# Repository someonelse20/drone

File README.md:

# drone
All the files for my drone project.

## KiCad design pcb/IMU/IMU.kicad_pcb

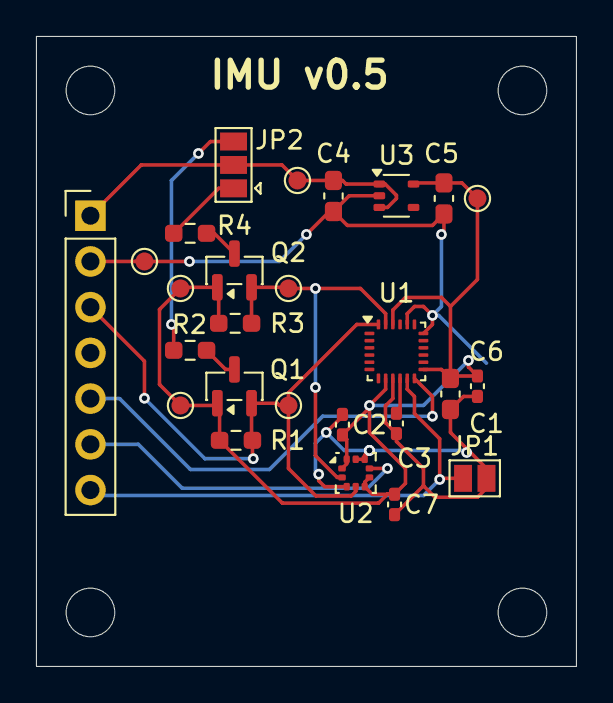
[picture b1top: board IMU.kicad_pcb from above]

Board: 2 copper layers, 30.0 x 35.0 mm, 26 parts (0 on the bottom side), 13 nets.

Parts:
C1, C4, C5: 1uf; C_0603_1608Metric_Pad1.08x0.95mm_HandSolder
C2, C3, C6, C7: 0.1uf; C_0402_1005Metric_Pad0.74x0.62mm_HandSolder
J1: Pin Bus; PinHeader_1x07_P2.54mm_Vertical
JP1: SolderJumper_2_Open; SolderJumper-2_P1.3mm_Open_Pad1.0x1.5mm
JP2: SolderJumper_3_Open; SolderJumper-3_P1.3mm_Open_Pad1.0x1.5mm
Q1, Q2: BSS84; SOT-23
R1, R2, R3, R4: 2.2k; R_0603_1608Metric_Pad0.98x0.95mm_HandSolder
TP1, TP2, TP3, TP4, TP5, TP6, TP7: TestPoint; TestPoint_Pad_D1.0mm
U1: ICM-20948; InvenSense_QFN-24_3x3mm_P0.4mm
U2: ST_HLGA-10_2x2mm_P0.5mm_LayoutBorder3x2y
U3: MIC5365-1.8YC5; SOT-353_SC-70-5

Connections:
/1.8v: C1.1, C2.1, C5.1, C6.1, C7.1, Q1.1 (G), Q2.1 (G), R1.1, R3.1, TP1.1, TP4.1, TP7.1, U1.8 (VDDIO), U1.13 (VDD), U1.22 (~CS), U2.1 (CS), U2.5 (VDD), U2.6 (SD0/AD0), U2.10 (VDDIO), U3.5 (VOUT)
/FSYNC: J1.7, JP1.1 (A), U1.11 (FSYNC)
/INT1: J1.5, U1.12 (INT1)
/INT2: J1.6, U2.7 (INT)
/SCL: J1.4, Q2.2 (S), R3.2, TP6.1, U1.23 (SCL/SCLK), U2.2 (SCL/SCLK)
/SDA: J1.3, Q1.2 (S), R1.2, TP2.1, U1.24 (SDA/SDI), U2.4 (SDA/SDIO/SDI)
/VIN: C4.1, J1.1, JP2.2 (C), TP3.1, U3.1 (VIN), U3.3 (EN)
GND: C1.2, C2.2, C3.2, C4.2, C5.2, C6.2, C7.2, J1.2, JP1.2 (B), TP5.1, U1.9 (SDO/AD0), U1.18 (GND), U1.20 (GND), U2.3, U2.8, U2.9, U3.2 (GND)
unnamed: JP2.1 (A), R4.1
unnamed: JP2.3 (B), R2.1
unnamed: Q1.3 (D), R2.2
unnamed: Q2.3 (D), R4.2
unnamed: C3.1, U1.10 (REGOUT)

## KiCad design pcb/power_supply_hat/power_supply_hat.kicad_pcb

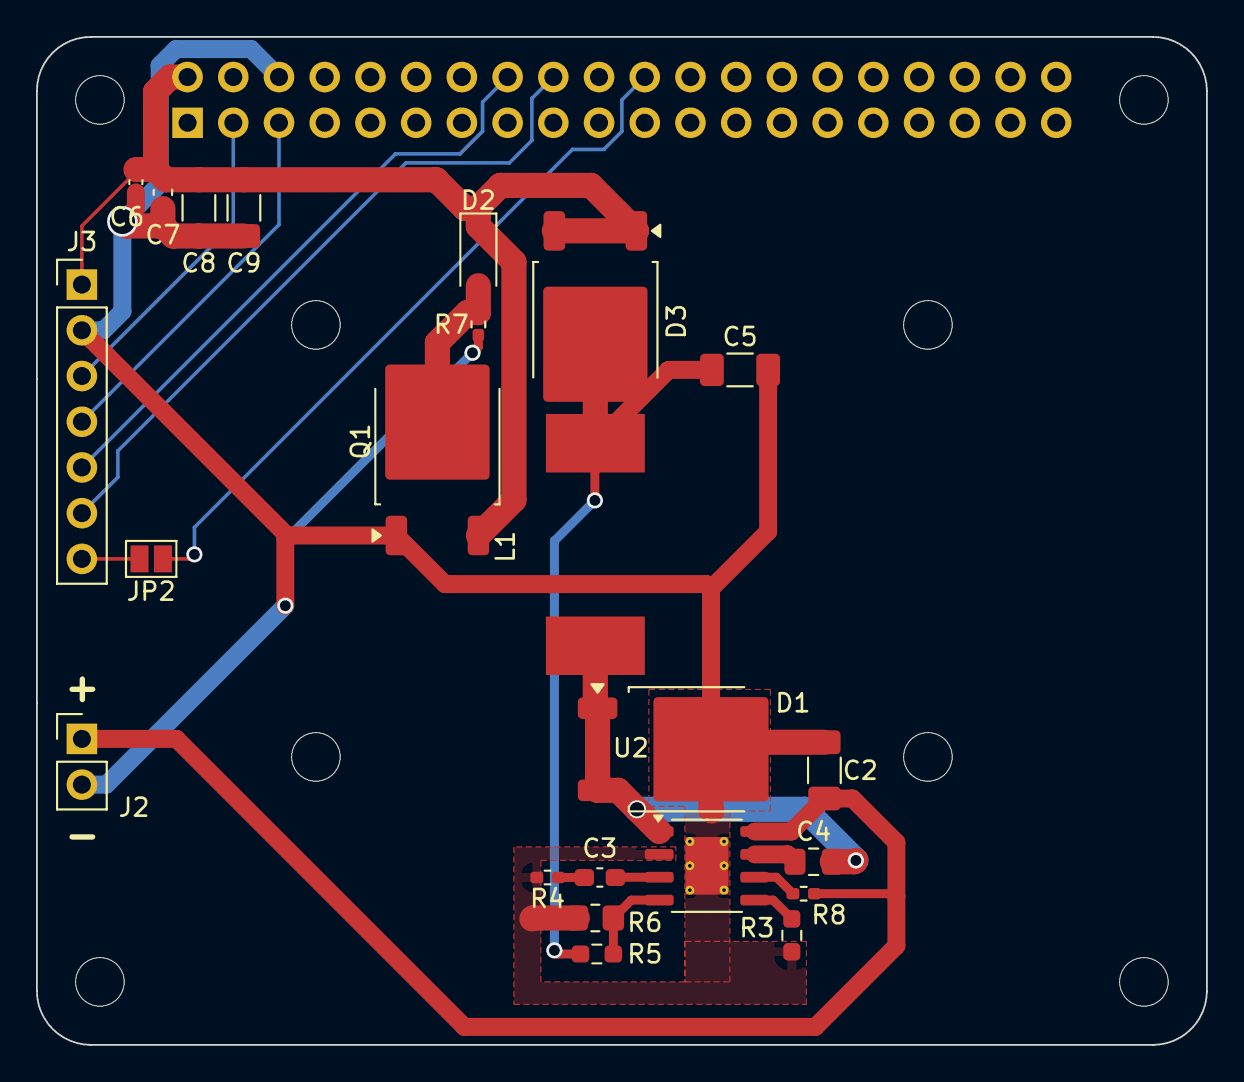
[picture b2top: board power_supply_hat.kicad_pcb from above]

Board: 2 copper layers, 65.0 x 56.0 mm, 28 parts (1 on the bottom side), 19 nets.

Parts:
C2, C8: 10uF; C_1206_3216Metric_Pad1.33x1.80mm_HandSolder
C3: 6800pF; C_0603_1608Metric_Pad1.08x0.95mm_HandSolder
C4: 0.1uF; C_0805_2012Metric_Pad1.18x1.45mm_HandSolder
C5, C9: 100uF; C_1206_3216Metric_Pad1.33x1.80mm_HandSolder
C6: 0.1uF; C_0402_1005Metric_Pad0.74x0.62mm_HandSolder
C7: 1uF; C_0603_1608Metric_Pad1.08x0.95mm_HandSolder
D1, D3: D_Schottky; TO-252-2
D2: D_Zener; D_SOD-123
J1: GPIO; PinSocket_2x20_P2.54mm_Vertical
J2: 12v; PinHeader_1x02_P2.54mm_Vertical
J3: IMU; PinHeader_1x07_P2.54mm_Vertical
JP2: SolderJumper_2_Open; SolderJumper-2_P1.3mm_Open_Pad1.0x1.5mm
L1: 33uH; 125CDMCC Inductor
MH1, MH2, MH3, MH4: MountingHole_2.7mm_M2.5
Q1: 2STD1665; TO-252-2
R3: 47k; R_0603_1608Metric_Pad0.98x0.95mm_HandSolder
R4: 10k; R_0402_1005Metric_Pad0.72x0.64mm_HandSolder
R5: 3k; R_0603_1608Metric_Pad0.98x0.95mm_HandSolder
R6: 0.75k; R_0805_2012Metric_Pad1.20x1.40mm_HandSolder
R7: 1k; R_0402_1005Metric_Pad0.72x0.64mm_HandSolder
R8: 100k; R_0402_1005Metric_Pad0.72x0.64mm_HandSolder
U2: BD9G341EFJ; HTSOP-8-1EP_3.9x4.9mm_P1.27mm_EP2.4x3.2mm_ThermalVias

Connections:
+3V3: J1.1, J1.17
+5V: C6.1, C7.1, C8.1, C9.1, D2.1 (K), D3.1 (K), D3.3, J1.2, J1.4, J3.1, Q1.3 (C)
/GPIO2/SDA1: J1.3, J3.3
/GPIO3/SCL1: J1.5, J3.4
/GPIO23: J1.16, J3.5
/GPIO24: J1.18, J3.6
/GPIO25: J1.22, JP2.1 (A)
GND: C2.2, C5.2, C6.2, C7.2, C8.2, C9.2, D1.2 (A), J1.6, J1.9, J1.14, J1.20, J1.25, J1.30, J1.34, J1.39, J2.2, J3.2, Q1.1 (E), R3.2, R4.2, R6.2, R7.2, U2.2 (GND), U2.9
unnamed: C3.2, R4.1
unnamed: C4.2, D1.1 (K), L1.1, U2.1 (LX)
unnamed: D2.2 (A), Q1.2 (B), R7.1
unnamed: C5.1, D3.2 (A), L1.2, R5.1
unnamed: C2.1, J2.1, R8.1, U2.8 (VCC)
unnamed: J3.7, JP2.2 (B)
unnamed: C4.1, U2.7 (BST)
unnamed: R8.2, U2.6 (EN)
unnamed: R5.2, R6.1, U2.4 (FB)
unnamed: R3.1, U2.5 (RT)
unnamed: C3.1, U2.3 (VC)

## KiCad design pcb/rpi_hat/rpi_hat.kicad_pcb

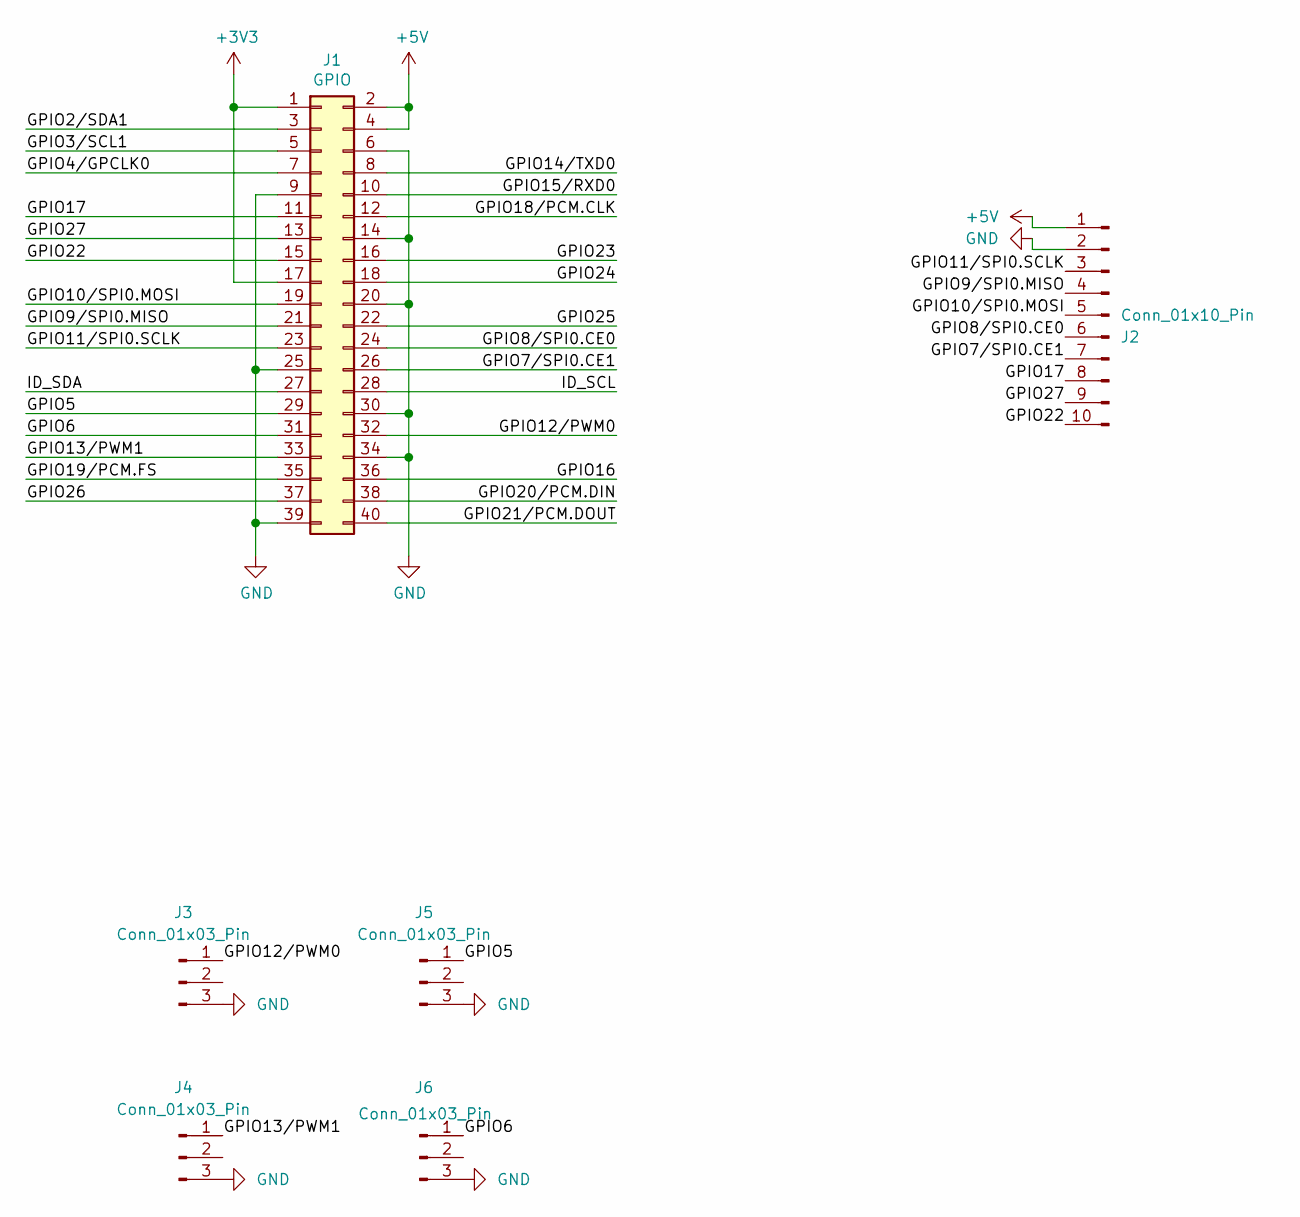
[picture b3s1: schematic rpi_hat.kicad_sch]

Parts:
J1: GPIO; PinSocket_2x20_P2.54mm_Vertical
J2: Conn_01x10_Pin; PinHeader_1x10_P2.54mm_Vertical
J3, J4, J5, J6: Conn_01x03_Pin; PinHeader_1x03_P2.54mm_Vertical

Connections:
+3V3: J1.1, J1.17
+5V: J1.2, J1.4, J2.1
/GPIO2/SDA1: J1.3
/GPIO3/SCL1: J1.5
/GPIO4/GPCLK0: J1.7
/GPIO5: J1.29, J5.1
/GPIO6: J1.31, J6.1
/GPIO7/SPI0.CE1: J1.26, J2.7
/GPIO8/SPI0.CE0: J1.24, J2.6
/GPIO9/SPI0.MISO: J1.21, J2.4
/GPIO10/SPI0.MOSI: J1.19, J2.5
/GPIO11/SPI0.SCLK: J1.23, J2.3
/GPIO12/PWM0: J1.32, J3.1
/GPIO13/PWM1: J1.33, J4.1
/GPIO14/TXD0: J1.8
/GPIO15/RXD0: J1.10
/GPIO16: J1.36
/GPIO17: J1.11, J2.8
/GPIO18/PCM.CLK: J1.12
/GPIO19/PCM.FS: J1.35
/GPIO20/PCM.DIN: J1.38
/GPIO21/PCM.DOUT: J1.40
/GPIO22: J1.15, J2.10
/GPIO23: J1.16
/GPIO24: J1.18
/GPIO25: J1.22
/GPIO26: J1.37
/GPIO27: J1.13, J2.9
/ID_SCL: J1.28
/ID_SDA: J1.27
GND: J1.6, J1.9, J1.14, J1.20, J1.25, J1.30, J1.34, J1.39, J2.2, J3.3, J4.3, J5.3, J6.3

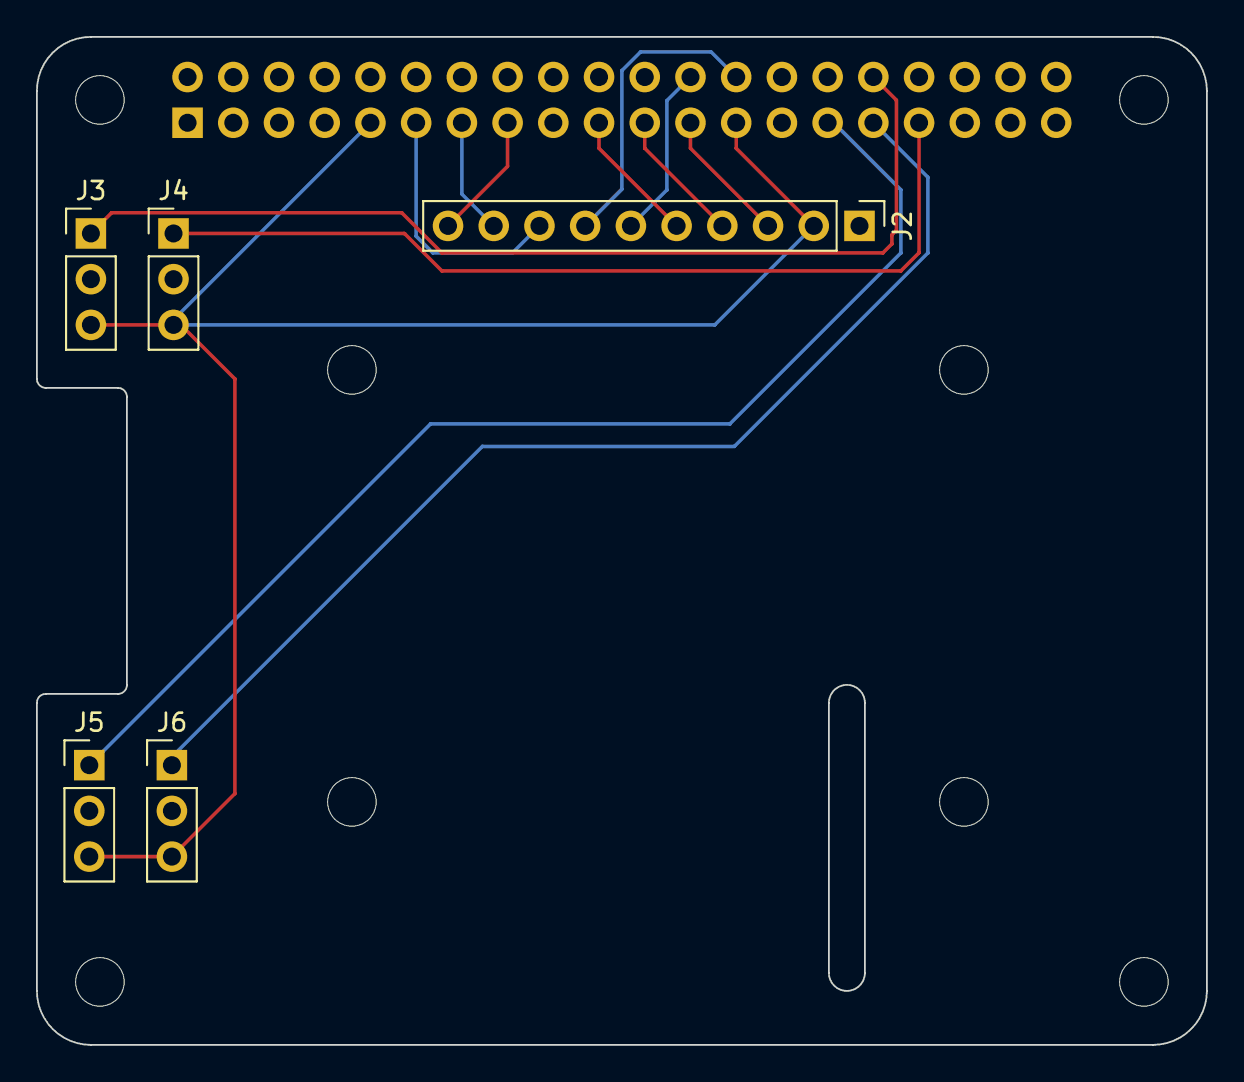
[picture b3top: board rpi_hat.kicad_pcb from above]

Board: 2 copper layers, 65.0 x 56.0 mm, 10 parts (1 on the bottom side), 15 nets.

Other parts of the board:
MH1, MH2, MH3, MH4: MountingHole_2.7mm_M2.5

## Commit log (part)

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2025-09-17 uploading all current files to git
2025-09-17 removed .vscode folders and changed .gitignore to only exclude build directories
2025-09-17 testing to make sure to remove build dirs
2025-09-17 removing last two build dirs
2025-09-18 Added Fusion and removed other repos
2025-09-18 testing test branch
2025-09-18 testing testing branch
2025-09-18 more testing
2025-09-23 started ahrs file
2025-09-24 removed unnesisary files
2025-09-26 added empty files
2025-09-26 started adding calibration to ahrs
2025-09-26 more work on calibration
2025-10-02 testing ahrs
2025-10-02 fixed library linking issues
2025-10-02 added schematic photo
2025-10-17 updated pcb
2025-11-02 IMU v0.5
2025-11-16 updated flight controller
2025-11-18 converted ahrs to be a class
2025-11-18 added gyro calibration
2025-11-19 converting vectors to structs
2025-11-22 debugging ahrs
2025-11-22 debuging ahrs
2025-11-30 updated calibration datasets
2025-11-30 added mag datasets
2025-12-03 recalibrating imu
2025-12-03 It's working! Mostly. Added gyro calibration to ahrs.
2025-12-03 completed accelerometer calibration
2025-12-03 integrated accelerometer calibration
2025-12-03 updated accel and mag calibration
2025-12-03 calibrating magnetometer, and something funky happened to cad exports.
2025-12-04 fixed heading calculation
2025-12-04 testing magnetometer calibration
2025-12-04 polishing up
2025-12-04 added on the fly gyro calibration
2025-12-04 added visualize_accel.py
2025-12-04 testing acceleration calculation
2025-12-05 adding code to transmit imu data
2025-12-05 adding imu data server
2025-12-05 adding imu data client and gyro graph
2025-12-05 added gyro graph
2025-12-06 fixed gyro error
2025-12-06 adding magnetometer ellipsoid calibration
2025-12-07 finished magnetometer ellipsoid calibration
2025-12-07 trying to get heading to work
2025-12-07 debuging heading
2025-12-07 added mx+
2025-12-07 debugging magnetometer calibration
2025-12-08 added m4
2025-12-08 updated visualize mag
2025-12-08 added m5
2025-12-29 added alignment magnetometer calibration
2026-01-01 got new clean magnetometer datasets
2026-01-01 added mx- to calibration data
2026-01-01 updated mag calibration
2026-01-01 changed calibration to -z
2026-01-01 IT WORKS
2026-01-01 fixed magnetometer orientation
2026-01-03 fixed acceleration
2026-01-03 recalibrating
2026-01-03 cleaned up mag calibration
2026-01-04 cleaned up
2026-01-05 added pid fiels
2026-01-17 testing motor control
2026-01-18 testing motor and cleaning up
2026-01-18 working on making lsm9ds1 driver
2026-01-19 added basic motor control
2026-01-19 added full motor functionality
2026-01-19 reoriented physical IMU
2026-01-19 reoriented IMU again
2026-01-20 added toto commet
2026-01-21 added custom lsm9ds1 driver
2026-01-21 configured delta time
2026-01-22 added microsecond accuracy to timestamp and changed dt to 0.002
2026-01-22 changed imu driver data rate format
2026-01-22 added json config
2026-01-24 cleaning up
2026-01-24 added cad designs
2026-01-24 exported cad models
2026-01-25 updated rod extention
2026-01-25 added rod cap
2026-01-26 testing drone
2026-01-26 added cad files and visualise pid
2026-01-27 testing pid
2026-01-29 created files to test ahrs alg
2026-01-30 refactored ahrs into seperate dir and added operators
